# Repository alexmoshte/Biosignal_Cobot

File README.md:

My final year project. A collaborative robotic arm controlled by sEMG signals as the main control input parameter. Here I upload the KICAD PCB design files of the motor drivers, the MCU which controls the drivers, the DAQ that picks up the sEMG signals from the muscles and the documentation for the project

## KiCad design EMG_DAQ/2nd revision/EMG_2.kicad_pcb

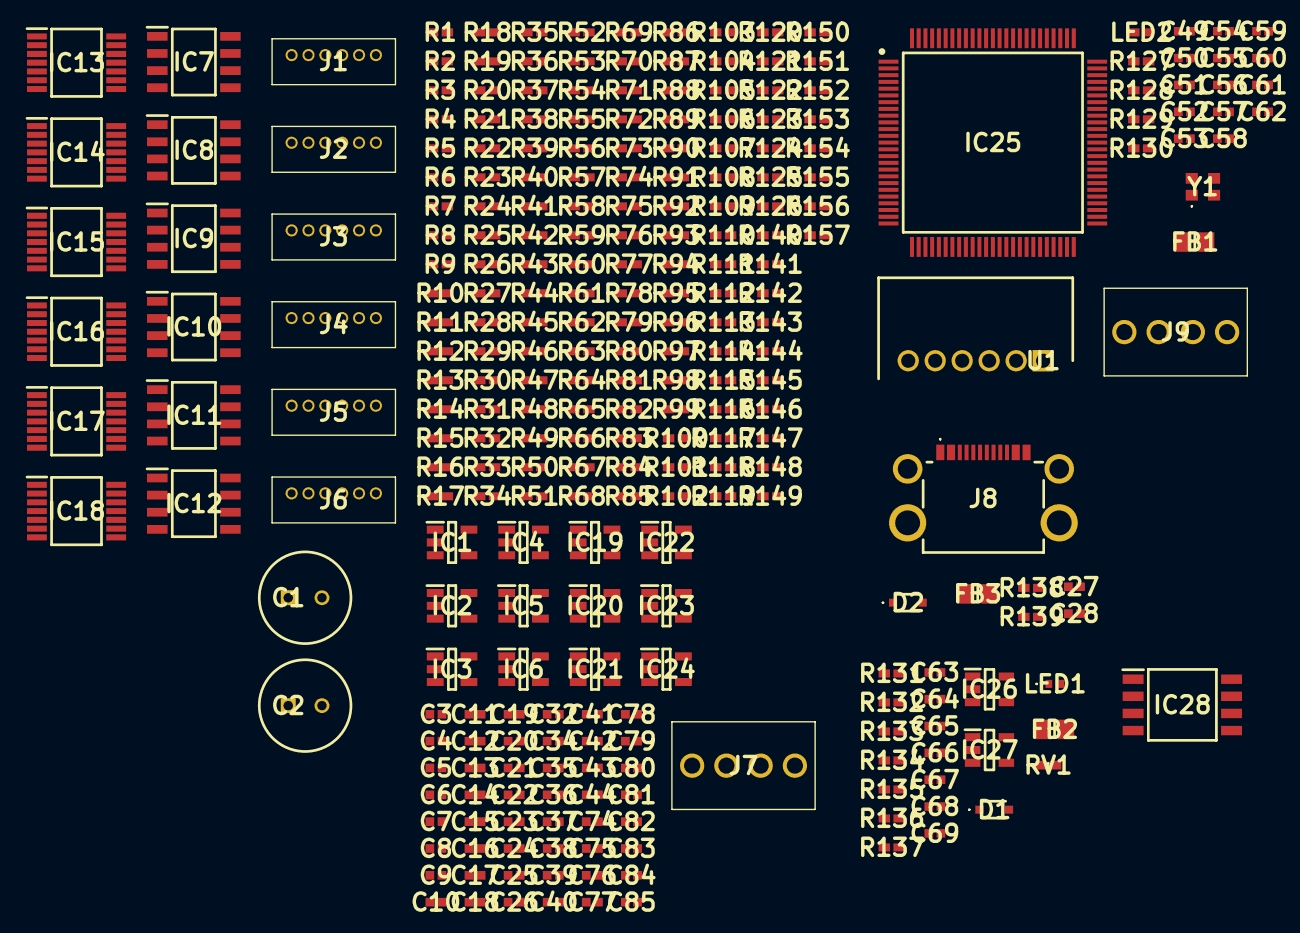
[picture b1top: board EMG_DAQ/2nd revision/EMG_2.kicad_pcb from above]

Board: 6 copper layers, 277 parts (0 on the bottom side), 47 nets, no tracks yet.

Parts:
C1, C2: C_pol_1uF/6V3; CAPPRD250W50D680H1250-Electrolytic
C3, C4, C5, C6, C7, C8, C9, C10, C11, C12, C13, C14, C66, C67, C68, C69: 1uF/6V3; 0402CAP
C15, C16, C17, C18, C19, C20, C21, C22, C23, C24, C25, C26: 0u1F/6V3; 0402CAP
C27, C28, C49, C50, C51, C52, C53, C54, C55, C56, C57, C58, C59: 100nF/6V3; 0402CAP
C32, C34, C35, C36, C37, C38: 12nF/6V3; 0402CAP
C39, C40, C41, C42, C43, C44: 82nF/6V3; 0402CAP
C60, C61, C62, C63, C64, C65: 100pF/6V3; 0402CAP
C74, C75, C76, C77, C78, C79: 30nF/6V3; 0402CAP
C80, C81, C82, C83, C84, C85: 33nF/6V3; 0402CAP
D1, D2: Schottky_BAT165AX; BAT165AX
FB1, FB2: 100R_BEADC0603X33N; BEADC2012X110N
FB3: 120R_BEADC0603X33N; BEADC2012X110N
IC1, IC2, IC3, IC4, IC5, IC6, IC19, IC20, IC21, IC22, IC23, IC24: IC_NCS21911SN2T1G; IC_NCS21911SN2T1
IC7, IC8, IC9, IC10, IC11, IC12: IC_AD620ARZ
IC13, IC14, IC15, IC16, IC17, IC18: IC_LM324PT; LM324_SOP65P640X120-14N
IC25: IC_STM32G4A1VET6; G4_QFP50P1600X1600X160-100N
IC26, IC27: IC_LDK320AM-R; LDO_SOT95P280X145-5N
IC28: IC_Flash_8MB_SST26WF064C-104I_SM; Flash_SOIC127P794X203-8N
J1, J2, J3, J4, J5, J6: 6P_Male_Conn_DF13-1.25DSA; 6p_male_DF136P125DSA
J7, J9: ScrewT_4P_282834-4; 4p_ScrewT_2828344
J8: USB-FS_2340901-1; USB-FS_23409011
LED1: LED_G; SMLP14ECNWT86-LED
LED2: LED_R; RES0402
R1, R2, R3, R4, R5, R6: 1M_1%; RES0402
R7, R8, R9, R10, R11, R12, R13, R14, R15, R16, R17, R18: 22K_1%; RES0402
R19, R20, R21, R22, R23, R24, R97, R98, R99, R100, R101, R102, R103, R104, R105, R106, R107, R108, R121, R122, R123, R124, R125, R126, R135, R140, R141, R142, R143, R144, R145, R146, R147, R148, R149, R150, R151, R152, R153, R154, R155, R156, R157: 10K; RES0402
R25, R26, R27, R28, R29, R30: 3K48; RES0402
R31, R32, R33, R34, R35, R36: 23K2; RES0402
R37, R38, R39, R40, R41, R42, R43, R44, R45, R46, R47, R48, R61, R63, R65, R67, R69, R71: 3K; RES0402
R49, R50, R51, R52, R53, R54: 95K3; RES0402
R55, R56, R57, R58, R59, R60: 82K; RES0402
R62, R64, R66, R68, R70, R72, R86, R88, R90, R92, R94, R96, R110, R112, R114, R116, R118, R120, R127, R128, R129, R130, R131, R132, R133, R134: 1K; RES0402
R73, R74, R75, R76, R77, R78, R79, R80, R81, R82, R83, R84: 5K36; RES0402
R85, R87, R89, R91, R93, R95, R109, R111, R113, R115, R117, R119: 2K; RES0402
R136: 47K; RES0402
R137: 91K; RES0402
R138, R139: 5K1; RES0402
RV1: ESDSupressor; VARC1005X41N_ESDsup
U1: 6p_SWD_Conn_DF3A-6P-2DS; SWD_header_SHDRRA6W60P0X200_1X6_1400X720X530P
Y1: XTAL_ABM10-16MHZ-D30-T3; ABM10_XTAL

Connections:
+3.3V: FB1.1, IC25.6 (VBAT), IC25.24 (VDD_1), IC25.49 (VDD_2), IC25.64 (VDD_3), IC25.75 (VDD_4), IC25.100 (VDD_5), IC26.4 (ADJ), IC27.1 (IN), IC27.4 (ADJ), IC28.8 (VDD), U1.6
+5V: D1.2, D2.1, FB2.2, FB3.1, FB3.2, IC26.1 (IN), J8.A4 (VBUS_1), J8.A9 (VBUS_2), LED1.2, RV1.2
+12V: C1.2, IC1.5 (V+), IC2.5 (V+), IC3.5 (V+), IC4.5 (V+), IC5.5 (V+), IC6.5 (V+), IC7.7 (Vs+), IC8.7 (Vs+), IC9.7 (Vs+), IC10.7 (Vs+), IC11.7 (Vs+), IC12.7 (Vs+), IC13.4 (V+), IC14.4 (V+), IC15.4 (V+), IC16.4 (V+), IC17.4 (V+), IC18.4 (V+), IC19.5 (V+), IC20.5 (V+), IC21.5 (V+), IC22.5 (V+), IC23.5 (V+), IC24.5 (V+), J7.1
-12V: C2.1, IC1.2 (V-), IC2.2 (V-), IC3.2 (V-), IC4.2 (V-), IC5.2 (V-), IC6.2 (V-), IC7.4 (Vs-), IC8.4 (Vs-), IC9.4 (Vs-), IC10.4 (Vs-), IC11.4 (Vs-), IC12.4 (Vs-), IC13.11 (V-), IC14.11 (V-), IC15.11 (V-), IC16.11 (V-), IC17.11 (V-), IC18.11 (V-), IC19.2 (V-), IC20.2 (V-), IC21.2 (V-), IC22.2 (V-), IC23.2 (V-), IC24.2 (V-), J7.4
/Analog Signal Conditioner (ASC)/ASC-OUT_1: IC21.1, IC23.1
/Analog Signal Conditioner (ASC)/OUT_4_1: IC15.14, IC17.14, IC21.3 (+), IC23.3 (+)
/Analog Signal Conditioner (ASC)/OUT_4_2: IC13.14, IC19.3 (+)
/Analog Signal Conditioner (ASC)/OUT_4_4: IC14.14, IC20.3 (+)
/Analog Signal Conditioner (ASC)/OUT_4_5: IC18.14, IC24.3 (+)
/Analog Signal Conditioner (ASC)/OUT_4_6: IC16.14, IC22.3 (+)
/FLASH/Chip-Enable-I/O: IC25.83 (PD1), IC28.1 (CE)
/FLASH/SPI3_SCK_Flash: IC25.79 (PC10), IC28.6 (SCK)
/FLASH/SPI3_SI_Flash: IC25.81 (PC12), IC28.5 (SI)
/FLASH/SPI3_SO_Flash: IC25.80 (PC11), IC28.2 (SO)
/FLASH/Write_Protect_I/O: IC25.85 (PD3), IC28.3 (WP)
/MCU/DAC1_OUT1_Osc: IC25.26 (PA4), J9.1
/MCU/DAC1_OUT2_Osc: IC25.27 (PA5), J9.4
/MCU/NRST: IC25.14 (PG10-NRST), U1.2
/MCU/SWCLK: IC25.77 (PA14), U1.4
/MCU/SWDIO: IC25.76 (PA13), U1.5
/MCU/SWO: IC25.90 (PB3), U1.3
/MCU/USB-FS_D_N: IC25.72 (PA11), J8.A7 (DN1), J8.B7 (DN2)
/MCU/USB-FS_D_P: IC25.73 (PA12), J8.A6 (DP1), J8.B6 (DP2)
EMG_1+: IC9.3 (+), J1.3
EMG_1-: IC9.2 (-), J1.1
EMG_2+: IC7.3 (+), J4.3
EMG_2-: IC7.2 (-), J4.1
EMG_3+: IC11.3 (+), J3.3
EMG_3-: IC11.2 (-), J3.1
EMG_4+: IC8.3 (+), J5.3
EMG_4-: IC8.2 (-), J5.1
EMG_5+: IC12.3 (+), J6.3
EMG_5-: IC12.2 (-), J6.1
EMG_6+: IC10.3 (+), J2.3
EMG_6-: IC10.2 (-), J2.1
GND: C1.1, C2.2, D2.2, IC1.3 (+), IC2.3 (+), IC3.3 (+), IC4.3 (+), IC5.3 (+), IC6.3 (+), IC25.23 (VSS_1), IC25.35 (VSSA), IC25.48 (VSS_2), IC25.63 (VSS_3), IC25.74 (VSS_4), IC25.99 (VSS_5), IC26.2 (GND), IC27.2 (GND), IC28.4 (VSS), J7.2, J7.3, J8.A1 (GND_1), J8.A12 (GND_2), J8.MH1, J8.MH2, J8.MH3, J8.MH4, J9.2, J9.3, RV1.1, U1.1, Y1.2 (GND_1), Y1.4 (GND_2)
unnamed: D1.1, FB2.1
unnamed: IC25.4 (PE5), LED2.2
unnamed: IC25.12 (PF0-OSC_IN), Y1.1 (X1)
unnamed: FB1.2, IC25.36 (VREF+), IC25.37 (VDDA)
unnamed: IC26.3 (EN), IC27.3 (EN)
REF_1: IC3.1, IC7.5 (Ref), IC9.5 (Ref), J1.5
REF_2: IC1.1, J4.5
REF_3: IC5.1, IC11.5 (Ref), J3.5
REF_4: IC2.1, IC8.5 (Ref), J5.5
REF_5: IC6.1, IC12.5 (Ref), J6.5
REF_6: IC4.1, IC10.5 (Ref), J2.5

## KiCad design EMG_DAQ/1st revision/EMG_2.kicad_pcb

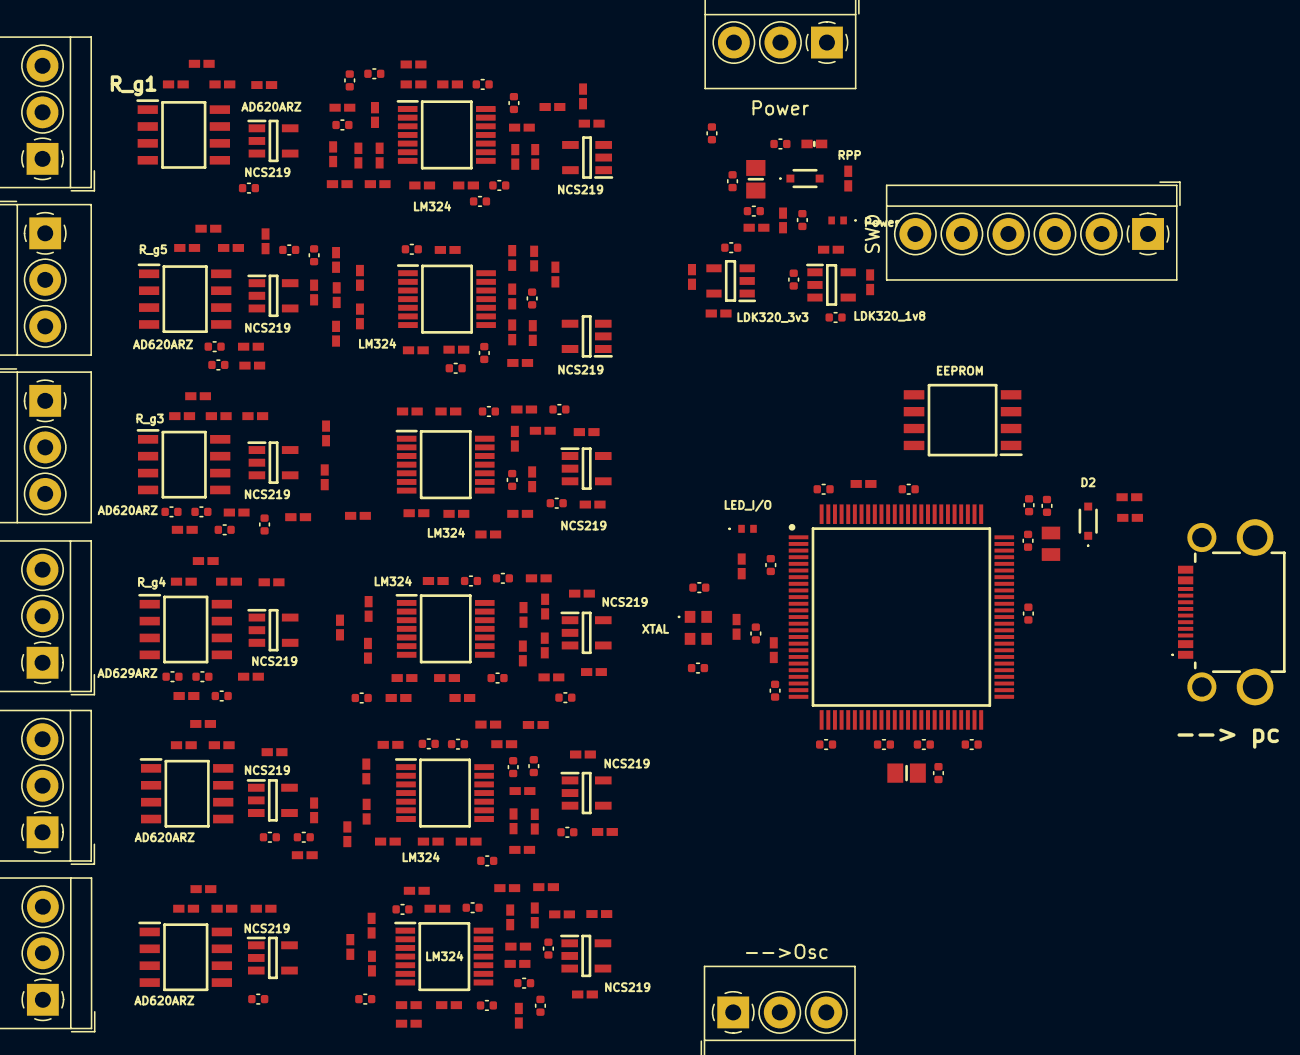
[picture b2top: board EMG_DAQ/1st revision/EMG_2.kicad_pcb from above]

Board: 6 copper layers, 264 parts (0 on the bottom side), 183 nets, no tracks yet.

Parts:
--> pc: 2340901-1_USB-FS; 23409011_USB-FS
-->Osc: --> Osc; TerminalBlock_4Ucon_1x03_P3.50mm_Horizontal
AD620ARZ, AD620ARZ#2, AD620ARZ#3, AD620ARZ#4, AD620ARZ#5, AD629ARZ: AD620ARZ; AD620
C1: 1uF/12V; C_0402_1005Metric
C2, C4, C6, C9, C11, C13, C14, C16, C18, C21, C23, C25, C67, C68, C69, C70: 1uF; C_0402_1005Metric
C3, C5, C7, C8, C10, C12, C15, C17, C19, C20, C22, C24: 0.1uF; C_0402_1005Metric
C26, C28, C30, C32, C38, C40: 33nF; C_0402_1005Metric
C27, C29, C31, C33, C39, C41: 30nF; C_0402_1005Metric
C34, C36, C42, C44, C46, C48: 82nF; C_0402_1005Metric
C35, C37, C43, C45, C47, C49: 12nF; C_0402_1005Metric
C50: 2u2F; C_0402_1005Metric
C51, C52, C53, C54, C55, C56, C57, C58, C59, C60: 100nF; C_0402_1005Metric
C61, C62, C63, C64, C65, C66: 100pF; C_0402_1005Metric
C71, C72: 100n; C_0402_1005Metric
CH1, CH2, CH3, CH4, CH5, CH6: Screw_Terminal; TerminalBlock_4Ucon_1x03_P3.50mm_Horizontal
D2: BAT165AX
EEPROM: Flash_SOIC127P794X203-8N
FB1, FB2: LI0805H151R-10; BEADC2012X110N
FB3: FB 120R; FBC2012X90N
IC14: LM324PT; LM324_SOP65P640X120-14N
IC20: NCS21911SN2T1G; Single Opamp
IC25: STM32G4A1VET6; G4_QFP50P1600X1600X160-100N
LDK320_1v8, LDK320_3v3: LDK320AM-R; LDO_SOT95P280X145-5N
LED_I/O: RED_LED; SMLP14ECNWT86-LED
LM324, LM324#2, LM324#3, LM324#4, LM324#5: LM324PT; LM324_SOP65P640X120-14N
NCS219, NCS219#2, NCS219#3, NCS219#4, NCS219#5, NCS219#6, NCS219#7, NCS219#8, NCS219#9, NCS219#10, NCS219#11: NCS21911SN2T1G; Single Opamp
Power: Green_LED; SMLP14ECNWT86-LED
Power#2: Screw_Terminal; TerminalBlock_4Ucon_1x03_P3.50mm_Horizontal
R1, R3, R5, R7, R9, R11, R13, R14, R15, R16, R17, R18: 22K_1%; RES0402
R2, R4, R6, R8, R10, R12: 1M_1%; RES0402
R19, R21, R23, R26, R28, R36: 3.48K; RES0402
R20, R22, R24, R25, R27, R29: 95.3k; RES0402
R30, R32, R34, R38, R40, R42: 23.2K; RES0402
R31, R33, R35, R37, R39, R41: 82k; RES0402
R43, R45, R47, R49, R51, R53, R55, R57, R59, R61, R63, R65: 3K; RES0402
R44, R46, R48, R50, R52, R54, R56, R58, R60, R62, R64, R66, R92, R94, R96, R98, R100, R102, R104, R106, R108, R110, R112, R114, R127, R128, R129, R130, R131, R132, R133, R135: 1K; RES0402
R67, R68, R69, R70, R73, R74, R79, R80, R81, R82, R85, R86: 10k; RES0402
R71, R72, R75, R76, R77, R78, R83, R84, R87, R88, R89, R90: 5.36K; RES0402
R91, R93, R95, R97, R99, R101, R103, R105, R107, R109, R111, R113: 2K; RES0402
R115, R117, R119, R121, R123, R125: 20K; RES0402
R116, R118, R120, R122, R124, R126, R134: 10K; RES0402
R136: 47K; RES0402
R137: 91K; RES0402
R138, R139: 5K1; RES0402
RPP: BAT165AX
RV1: ESD-Supresssor; VARC1005X41N_ESDsup
R_g1, R_g3, R_g4, R_g5: 10K; RES0402
R_gain4, R_gain6: 10K; RES0402
SWD: TerminalBlock_4Ucon_1x06_P3.50mm_Horizontal
XTAL: ABM10-16.000MHZ-D30-T3; ABM10_XTAL

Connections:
+1.8V: C70.1, EEPROM.8 (VDD), LDK320_1v8.4 (ADJ), R136.1
+3.3V: C50.1, C51.1, C52.1, C53.1, C54.1, C55.1, C56.1, C57.1, C59.1, C68.1, C69.1, FB1.1, IC25.6 (VBAT), IC25.24 (VDD_1), IC25.49 (VDD_2), IC25.64 (VDD_3), IC25.75 (VDD_4), IC25.100 (VDD_5), LDK320_1v8.1 (IN), LDK320_3v3.4 (ADJ), R128.1, R133.1, SWD.6 (+VCC)
+5V: --> pc.A4 (VBUS_1), C65.1, C67.1, C71.1, C72.1, D2.1, FB2.2, FB3.1, FB3.2, LDK320_3v3.1 (IN), Power.2, Power#2.1, R131.1, RPP.2, RV1.2
+12V: AD620ARZ.7 (+VS), AD620ARZ#2.7 (+VS), AD620ARZ#3.7 (+VS), AD620ARZ#4.7 (+VS), AD620ARZ#5.7 (+VS), AD629ARZ.7 (+VS), IC14.4 (VCC+), IC20.5 (VDD), LM324.4 (VCC+), LM324#2.4 (VCC+), LM324#3.4 (VCC+), LM324#4.4 (VCC+), LM324#5.4 (VCC+), NCS219.5 (VDD), NCS219#2.5 (VDD), NCS219#3.5 (VDD), NCS219#4.5 (VDD), NCS219#5.5 (VDD), NCS219#6.5 (VDD), NCS219#7.5 (VDD), NCS219#8.5 (VDD), NCS219#9.5 (VDD), NCS219#10.5 (VDD), NCS219#11.5 (VDD)
-12V: AD620ARZ.4 (-VS), AD620ARZ#2.4 (-VS), AD620ARZ#3.4 (-VS), AD620ARZ#4.4 (-VS), AD620ARZ#5.4 (-VS), AD629ARZ.4 (-VS), C1.2, IC14.11 (VCC-), IC20.2 (VSS), LM324.11 (VCC-), LM324#2.11 (VCC-), LM324#3.11 (VCC-), LM324#4.11 (VCC-), LM324#5.11 (VCC-), NCS219.2 (VSS), NCS219#2.2 (VSS), NCS219#3.2 (VSS), NCS219#4.2 (VSS), NCS219#5.2 (VSS), NCS219#6.2 (VSS), NCS219#7.2 (VSS), NCS219#8.2 (VSS), NCS219#9.2 (VSS), NCS219#10.2 (VSS), NCS219#11.2 (VSS)
/Analog Signal Conditioner (ASC)/ASC->ADC_1_USER1: IC25.20 (PA0), NCS219#10.1 (OUT)
/Analog Signal Conditioner (ASC)/ASC->ADC_1_USER2: IC25.21 (PA1), NCS219#9.1 (OUT), R115.2
/Analog Signal Conditioner (ASC)/ASC->ADC_2_USER1: IC20.1 (OUT), IC25.28 (PA6), R117.2
/Analog Signal Conditioner (ASC)/ASC->ADC_2_USER2: IC25.29 (PA7), NCS219#6.1 (OUT), R119.2
/Analog Signal Conditioner (ASC)/ASC->ADC_3_USER1: IC25.33 (PB1), NCS219#7.1 (OUT), R123.2
/Analog Signal Conditioner (ASC)/ASC->ADC_3_USER2: IC25.40 (PE9), NCS219#5.1 (OUT), R125.2
/Analog Signal Conditioner (ASC)/IN+1_1: C16.2, LM324#5.3 (IN+1), R21.1
/Analog Signal Conditioner (ASC)/IN+1_2: C18.2, LM324#4.3 (IN+1), LM324#4.8 (OUT_3), R23.1
/Analog Signal Conditioner (ASC)/IN+1_3: C25.2, IC14.3 (IN+1), R36.1
/Analog Signal Conditioner (ASC)/IN+1_4: C21.2, LM324#3.3 (IN+1), R26.1
/Analog Signal Conditioner (ASC)/IN+1_5: C23.2, LM324.3 (IN+1), R28.1
/Analog Signal Conditioner (ASC)/IN+1_6: C14.2, LM324#2.3 (IN+1), R19.1
/Analog Signal Conditioner (ASC)/IN+2_1: C17.2, LM324#5.5 (IN+2), R22.1
/Analog Signal Conditioner (ASC)/IN+2_2: C19.2, LM324#4.5 (IN+2), R24.1
/Analog Signal Conditioner (ASC)/IN+2_3: C20.2, IC14.5 (IN+2), R25.1
/Analog Signal Conditioner (ASC)/IN+2_4: C22.2, LM324#3.5 (IN+2), R27.1
/Analog Signal Conditioner (ASC)/IN+2_5: C24.2, LM324.5 (IN+2), R29.1
/Analog Signal Conditioner (ASC)/IN+2_6: C15.2, LM324#2.5 (IN+2), R20.1
/Analog Signal Conditioner (ASC)/IN+3_1: C45.2, LM324#5.10 (IN+3), R88.2
/Analog Signal Conditioner (ASC)/IN+3_2: C35.2, LM324#4.10 (IN+3), R83.2
/Analog Signal Conditioner (ASC)/IN+3_3: C37.2, IC14.10 (IN+3), R84.2
/Analog Signal Conditioner (ASC)/IN+3_4: C43.2, LM324#3.10 (IN+3), R87.2
/Analog Signal Conditioner (ASC)/IN+3_5: C47.2, LM324.10 (IN+3), R89.2
/Analog Signal Conditioner (ASC)/IN+3_6: C49.2, LM324#2.10 (IN+3), R90.2
/Analog Signal Conditioner (ASC)/IN+4_1: C33.2, LM324#5.12 (IN+4), R82.2
/Analog Signal Conditioner (ASC)/IN+4_2: C27.2, LM324#4.12 (IN+4), R79.2
/Analog Signal Conditioner (ASC)/IN+4_3: C29.2, IC14.12 (IN+4), R80.2
/Analog Signal Conditioner (ASC)/IN+4_4: C31.2, LM324#3.12 (IN+4), R81.2
/Analog Signal Conditioner (ASC)/IN+4_5: C39.2, LM324.12 (IN+4), R85.2
/Analog Signal Conditioner (ASC)/IN+4_6: C41.2, LM324#2.12 (IN+4), R86.2
/Analog Signal Conditioner (ASC)/IN-1_1: LM324#5.2 (IN-1), R47.1, R48.2
/Analog Signal Conditioner (ASC)/IN-1_2: LM324#4.2 (IN-1), R51.1, R52.2
/Analog Signal Conditioner (ASC)/IN-1_3: IC14.2 (IN-1), R65.1, R66.2
/Analog Signal Conditioner (ASC)/IN-1_3_1: NCS219#10.4 (IN-), R121.1, R122.2
/Analog Signal Conditioner (ASC)/IN-1_3_2: NCS219#9.4 (IN-), R115.1, R116.2
/Analog Signal Conditioner (ASC)/IN-1_3_3: IC20.4 (IN-), R117.1, R118.2
/Analog Signal Conditioner (ASC)/IN-1_3_4: NCS219#6.4 (IN-), R119.1, R120.2
/Analog Signal Conditioner (ASC)/IN-1_3_5: NCS219#7.4 (IN-), R123.1, R124.2
/Analog Signal Conditioner (ASC)/IN-1_3_6: NCS219#5.4 (IN-), R125.1, R126.2
/Analog Signal Conditioner (ASC)/IN-1_4: LM324#3.2 (IN-1), R57.1, R58.2
/Analog Signal Conditioner (ASC)/IN-1_5: LM324.2 (IN-1), R61.1, R62.2
/Analog Signal Conditioner (ASC)/IN-1_6: LM324#2.2 (IN-1), R43.1, R44.2
/Analog Signal Conditioner (ASC)/IN-2_1: LM324#5.6 (IN-2), R49.1, R50.2
/Analog Signal Conditioner (ASC)/IN-2_2: LM324#4.6 (IN-2), R53.1, R54.2
/Analog Signal Conditioner (ASC)/IN-2_3: IC14.6 (IN-2), R55.1, R56.2
/Analog Signal Conditioner (ASC)/IN-2_4: LM324#3.6 (IN-2), R59.1, R60.2
/Analog Signal Conditioner (ASC)/IN-2_5: LM324.6 (IN-2), R63.1, R64.2
/Analog Signal Conditioner (ASC)/IN-2_6: LM324#2.6 (IN-2), R45.1, R46.2
/Analog Signal Conditioner (ASC)/IN-3_1: LM324#5.9 (IN-3), R109.1, R110.2
/Analog Signal Conditioner (ASC)/IN-3_2: LM324#4.9 (IN-3), R99.1, R100.2
/Analog Signal Conditioner (ASC)/IN-3_3: IC14.9 (IN-3), R101.1, R102.2
/Analog Signal Conditioner (ASC)/IN-3_4: LM324#3.9 (IN-3), R107.1, R108.2
/Analog Signal Conditioner (ASC)/IN-3_5: LM324.9 (IN-3), R111.1, R112.2
/Analog Signal Conditioner (ASC)/IN-3_6: LM324#2.9 (IN-3), R113.1, R114.2
/Analog Signal Conditioner (ASC)/IN-4_1: LM324#5.13 (IN-4), R97.1, R98.2
/Analog Signal Conditioner (ASC)/IN-4_2: LM324#4.13 (IN-4), R91.1, R92.2
/Analog Signal Conditioner (ASC)/IN-4_3: IC14.13 (IN-4), R93.1, R94.2
/Analog Signal Conditioner (ASC)/IN-4_4: LM324#3.13 (IN-4), R95.1, R96.2
/Analog Signal Conditioner (ASC)/IN-4_5: LM324.13 (IN-4), R103.1, R104.2
/Analog Signal Conditioner (ASC)/IN-4_6: LM324#2.13 (IN-4), R105.1, R106.2
/Analog Signal Conditioner (ASC)/OUT_1_1: C5.1, LM324#5.1 (OUT_1), R32.2, R47.2
/Analog Signal Conditioner (ASC)/OUT_1_2: C7.1, LM324#4.1 (OUT_1), R34.2, R51.2
/Analog Signal Conditioner (ASC)/OUT_1_3: C8.1, IC14.1 (OUT_1), R42.2, R65.2
/Analog Signal Conditioner (ASC)/OUT_1_4: C10.1, LM324#3.1 (OUT_1), R38.2, R57.2
/Analog Signal Conditioner (ASC)/OUT_1_5: C12.1, LM324.1 (OUT_1), R40.2, R61.2
/Analog Signal Conditioner (ASC)/OUT_1_6: C3.1, LM324#2.1 (OUT_1), R30.2, R43.2
/Analog Signal Conditioner (ASC)/OUT_2_1: LM324#5.7 (OUT_2), R33.2, R49.2, R76.1
/Analog Signal Conditioner (ASC)/OUT_2_2: LM324#4.7 (OUT_2), R35.2, R53.2, R71.1
/Analog Signal Conditioner (ASC)/OUT_2_3: IC14.7 (OUT_2), R37.2, R55.2, R72.1
/Analog Signal Conditioner (ASC)/OUT_2_4: LM324#3.7 (OUT_2), R39.2, R59.2, R75.1
/Analog Signal Conditioner (ASC)/OUT_2_5: LM324.7 (OUT_2), R41.2, R63.2, R77.1
/Analog Signal Conditioner (ASC)/OUT_2_6: LM324#2.7 (OUT_2), R31.2, R45.2, R78.1
/Analog Signal Conditioner (ASC)/OUT_3_1: C44.2, LM324#5.8 (OUT_3), R70.1, R109.2
/Analog Signal Conditioner (ASC)/OUT_3_2: C34.2, R67.1, R99.2
/Analog Signal Conditioner (ASC)/OUT_3_3: C36.2, IC14.8 (OUT_3), R68.1, R101.2
/Analog Signal Conditioner (ASC)/OUT_3_4: C42.2, LM324#3.8 (OUT_3), R69.1, R107.2
/Analog Signal Conditioner (ASC)/OUT_3_5: C46.2, LM324.8 (OUT_3), R73.1, R111.2
/Analog Signal Conditioner (ASC)/OUT_3_6: C48.2, LM324#2.8 (OUT_3), R74.1, R113.2
/Analog Signal Conditioner (ASC)/OUT_4_1: C32.2, LM324#5.14 (OUT_4), NCS219#10.3 (IN+), R97.2
/Analog Signal Conditioner (ASC)/OUT_4_2: C26.2, LM324#4.14 (OUT_4), NCS219#9.3 (IN+), R91.2
/Analog Signal Conditioner (ASC)/OUT_4_3: C28.2, IC14.14 (OUT_4), IC20.3 (IN+), R93.2
/Analog Signal Conditioner (ASC)/OUT_4_4: C30.2, LM324#3.14 (OUT_4), NCS219#6.3 (IN+), R95.2
/Analog Signal Conditioner (ASC)/OUT_4_5: C38.2, LM324.14 (OUT_4), NCS219#7.3 (IN+), R103.2
/Analog Signal Conditioner (ASC)/OUT_4_6: C40.2, LM324#2.14 (OUT_4), NCS219#5.3 (IN+), R105.2
/Analog Signal Conditioner (ASC)/OUT_INS_1: AD620ARZ#5.6 (OUTPUT), C4.1
/Analog Signal Conditioner (ASC)/OUT_INS_2: AD620ARZ#3.6 (OUTPUT), C6.1
/Analog Signal Conditioner (ASC)/OUT_INS_3: AD620ARZ#2.6 (OUTPUT), C13.1
/Analog Signal Conditioner (ASC)/OUT_INS_4: AD629ARZ.6 (OUTPUT), C9.1
/Analog Signal Conditioner (ASC)/OUT_INS_5: AD620ARZ.6 (OUTPUT), C11.1
/Analog Signal Conditioner (ASC)/OUT_INS_6: AD620ARZ#4.6 (OUTPUT), C2.1
/FLASH/Chip-Enable-I/O: EEPROM.1 (CE), IC25.83 (PD1)
/FLASH/SPI3_SCK_Flash: EEPROM.6 (SCK), IC25.79 (PC10)
/FLASH/SPI3_SI_Flash: EEPROM.5 (SI), IC25.81 (PC12)
/FLASH/SPI3_SO_Flash: EEPROM.2 (SO), IC25.80 (PC11)
/FLASH/Write_Protect_I/O: EEPROM.3 (WP), IC25.85 (PD3)
/MCU/DAC1_OUT1_Osc: -->Osc.1, IC25.26 (PA4)
/MCU/DAC1_OUT2_Osc: -->Osc.3, IC25.27 (PA5)
/MCU/NRST: C63.1, IC25.14 (PG10-NRST), R128.2, SWD.2 (NRST)
/MCU/SWCLK: IC25.77 (PA14), SWD.4 (SWCLK)
/MCU/SWDIO: IC25.76 (PA13), SWD.5 (SWDIO)
/MCU/SWO: IC25.90 (PB3), SWD.3 (SWO)
/MCU/USB-FS_D_N: --> pc.A7 (DN1), --> pc.B7 (DN2), IC25.72 (PA11)
/MCU/USB-FS_D_P: --> pc.A6 (DP1), --> pc.B6 (DP2), IC25.73 (PA12)
EMG_1+: AD620ARZ#5.3 (+IN), CH1.2
EMG_1-: AD620ARZ#5.2 (-IN), CH1.3
EMG_2+: AD620ARZ#3.3 (+IN), CH2.2
EMG_2-: AD620ARZ#3.2 (-IN), CH2.3
EMG_3+: AD620ARZ#2.3 (+IN), CH3.2
EMG_3-: AD620ARZ#2.2 (-IN), CH3.3
EMG_4+: AD629ARZ.3 (+IN), CH4.2
EMG_4-: AD629ARZ.2 (-IN), CH4.3
EMG_5+: AD620ARZ.3 (+IN), CH5.2
EMG_5-: AD620ARZ.2 (-IN), CH5.3
EMG_6+: AD620ARZ#4.3 (+IN), CH6.2
EMG_6-: AD620ARZ#4.2 (-IN), CH6.3
GND: --> pc.A1 (GND_1), --> pc.A12 (GND_2), --> pc.MH1, --> pc.MH2, --> pc.MH3, --> pc.MH4, AD620ARZ#5.5 (REF), C1.1, C27.1, C29.1, C31.1, C33.1, C35.1, C37.1, C39.1, C41.1, C43.1, C45.1, C47.1, C49.1, C50.2, C51.2, C52.2, C53.2, C54.2, C55.2, C56.2, C57.2, C58.2, C59.2, C60.2, C61.2, C62.2, C63.2, C64.2, C65.2, C66.2, C67.2, C68.2, C69.2, C70.2, C71.2, C72.2, D2.2, EEPROM.4 (VSS), IC25.23 (VSS_1), IC25.35 (VSSA), IC25.48 (VSS_2), IC25.63 (VSS_3), IC25.74 (VSS_4), IC25.99 (VSS_5), LDK320_1v8.2 (GND), LDK320_3v3.2 (GND), NCS219.3 (IN+), NCS219#2.3 (IN+), NCS219#3.3 (IN+), NCS219#4.3 (IN+), NCS219#8.3 (IN+), NCS219#11.3 (IN+), Power#2.2, R19.2, R20.2, R21.2, R22.2, R23.2, R24.2, R25.2, R26.2, R27.2, R28.2, R29.2, R36.2, R44.1, R46.1, R48.1, R50.1, R52.1, R54.1, R56.1, R58.1, R60.1, R62.1, R64.1, R66.1, R92.1, R94.1, R96.1, R98.1, R100.1, R102.1, R104.1, R106.1, R108.1, R110.1, R112.1, R114.1, R116.1, R118.1, R120.1, R122.1, R124.1, R126.1, R129.2, R130.2, R132.2, R134.2, R135.2, R137.2, R138.1, R139.1, RV1.1, SWD.1 (GND), XTAL.2 (GND_1), XTAL.4 (GND_2)
unnamed: C10.2, C22.1, R39.1
unnamed: C11.2, C23.1, R40.1
unnamed: C12.2, C24.1, R41.1
unnamed: C13.2, C25.1, R42.1
unnamed: C2.2, C14.1, R30.1
unnamed: C3.2, C15.1, R31.1
unnamed: C4.2, C16.1, R32.1
unnamed: C5.2, C17.1, R33.1
unnamed: C6.2, C18.1, R34.1
unnamed: C7.2, C19.1, R35.1
unnamed: C8.2, C20.1, R37.1
unnamed: C9.2, C21.1, R38.1
unnamed: C26.1, R67.2, R79.1
unnamed: C28.1, R68.2, R80.1
unnamed: C30.1, R69.2, R81.1
unnamed: C32.1, R70.2, R82.1
unnamed: C34.1, R71.2, R83.1
unnamed: C36.1, R72.2, R84.1
unnamed: C38.1, R73.2, R85.1
unnamed: C40.1, R74.2, R86.1
unnamed: C42.1, R75.2, R87.1
unnamed: C44.1, R76.2, R88.1
unnamed: C46.1, R77.2, R89.1
unnamed: C48.1, R78.2, R90.1
unnamed: C64.1, FB2.1, RPP.1
unnamed: AD620ARZ#5.1 (RG_1), R13.1, R_g1.2
unnamed: AD620ARZ#5.8 (RG_2), R1.1, R_g1.1
unnamed: AD620ARZ#2.1 (RG_1), R15.1, R_g3.2
unnamed: AD620ARZ#2.8 (RG_2), R5.1, R_g3.1
unnamed: AD629ARZ.1 (RG_1), R16.1, R_g4.2
unnamed: AD629ARZ.8 (RG_2), R7.1, R_g4.1
unnamed: AD620ARZ.1 (RG_1), R17.1, R_gain4.2
unnamed: AD620ARZ.8 (RG_2), R9.1, R_gain4.1
unnamed: AD620ARZ#3.1 (RG_1), R14.1, R_g5.2
unnamed: AD620ARZ#3.8 (RG_2), R3.1, R_g5.1
unnamed: AD620ARZ#4.1 (RG_1), R18.1, R_gain6.2
unnamed: AD620ARZ#4.8 (RG_2), R11.1, R_gain6.1
unnamed: NCS219#2.4 (IN-), R1.2, R2.1, R13.2
unnamed: NCS219#8.4 (IN-), R3.2, R4.1, R14.2
unnamed: NCS219#3.4 (IN-), R5.2, R6.1, R15.2
unnamed: NCS219.4 (IN-), R7.2, R8.1, R16.2
unnamed: NCS219#4.4 (IN-), R9.2, R10.1, R17.2
unnamed: NCS219#11.4 (IN-), R11.2, R12.1, R18.2
unnamed: IC25.95 (PB8-BOOT0), R129.1
unnamed: IC25.4 (PE5), LED_I/O.2
unnamed: C61.1, IC25.12 (PF0-OSC_IN), XTAL.1 (X1)
unnamed: IC25.13 (PF1-OSC_OUT), R127.2
unnamed: C58.1, C60.1, FB1.2, IC25.36 (VREF+), IC25.37 (VDDA)
unnamed: C66.1, LDK320_1v8.3 (EN), LDK320_3v3.3 (EN), R131.2, R132.1
unnamed: LDK320_3v3.5 (OUT), R133.2, R134.1
unnamed: LDK320_1v8.5 (OUT), R136.2, R137.1
unnamed: --> pc.A5 (CC1), R139.2
unnamed: --> pc.B5 (CC2), R138.2
unnamed: Power.1, R130.1
unnamed: LED_I/O.1, R135.1
unnamed: C62.1, R127.1, XTAL.3 (X2)
REF_1: CH1.1, NCS219#2.1 (OUT), R2.2
REF_2: AD620ARZ#3.5 (REF), CH2.1, NCS219#8.1 (OUT), R4.2
REF_3: AD620ARZ#2.5 (REF), CH3.1, NCS219#3.1 (OUT), R6.2
REF_4: AD629ARZ.5 (REF), CH4.1, NCS219.1 (OUT), R8.2
REF_5: AD620ARZ.5 (REF), CH5.1, NCS219#4.1 (OUT), R10.2
REF_6: AD620ARZ#4.5 (REF), CH6.1, NCS219#11.1 (OUT), R12.2

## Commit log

2024-02-27 PCB design files and documentation added
2024-02-27 Files deleted
2024-02-27 Kicad design files and documentation added
